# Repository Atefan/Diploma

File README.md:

# Entropy — Hardware True Random Number Generator

ELSYS Sofia diploma project.

## The problem

Computers are deterministic — they can only produce pseudo-random numbers,
which is not good enough for real cryptographic or security-sensitive use
(secure communications, bank transfers, key generation, etc.). This project
builds a **true hardware entropy source** and feeds it directly into the
Linux kernel's entropy pool, so real applications get genuine randomness
instead of PRNG output.

## How it works

1. **Analog front-end** — a custom white-noise generation circuit (charge-pump
   voltage multiplier + PWM stage, op-amp) produces physical noise, sampled
   through the ADC. Schematic and PCB in `Pico_PCB/`.
2. **Firmware** (`Entropy device/`) — runs on a **Raspberry Pi Pico (RP2040,
   dual-core)**. One core samples the ADC and drives the PWM/noise circuit;
   the noise is buffered in a circular queue and streamed to the host over
   USB. Built with the Pico SDK + CMake.
3. **Linux kernel driver** (`driver/`) — a USB driver (`usb_entropy` module)
   that reads the incoming stream and exposes it as `/dev/entropy`, feeding
   it straight into the kernel's entropy pool via `linux/random.h`.
4. **GUI** (`GUI/`) — an SDL2-based Windows app that visualizes the live
   entropy output in real time.
5. **Validation** (`testing/`) — randomness was verified with the NIST Statistical Test Suite (STS 2.1.2, vendored here).

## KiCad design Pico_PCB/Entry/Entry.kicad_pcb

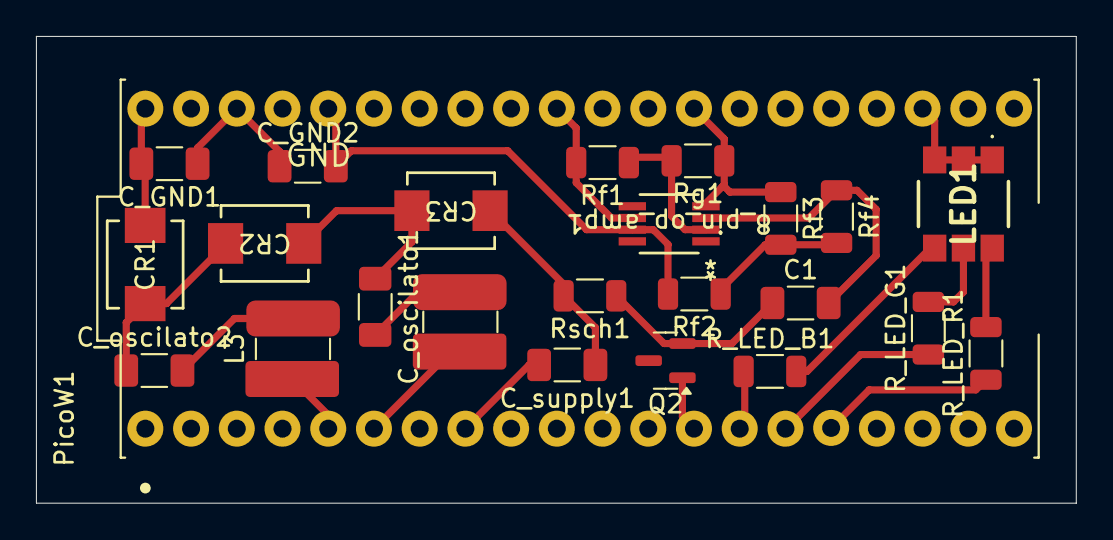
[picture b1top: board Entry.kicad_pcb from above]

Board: 2 copper layers, 57.8 x 25.9 mm, 24 parts (0 on the bottom side), 25 nets.

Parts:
8_pin_op_amp1: MCP6L91RT-EMS; MSOP8_MC_MCH
C1: .1uF; C_1206_3216Metric_Pad1.33x1.80mm_HandSolder
CR1, CR2, CR3: MBRS1100T3G; SMB_403A-03_ONS
C_GND1, C_GND2: .1uF; C_1206_3216Metric_Pad1.33x1.80mm_HandSolder
C_oscilato1, C_oscilato2: .1uF; C_1206_3216Metric_Pad1.33x1.80mm_HandSolder
C_supply1: .1uF; C_1206_3216Metric_Pad1.33x1.80mm_HandSolder
L1, L3: L; L_Coilcraft_LPS4414
LED1: MP008253
PicoW1: SC0918; MODULE_SC0918
Q2: 2n3904; SOT-23
R_LED_B1: 220; R_1206_3216Metric
R_LED_G1: 220; R_1206_3216Metric
R_LED_R1: 220; R_1206_3216Metric
Rf1: 680k; R_1206_3216Metric
Rf2: 120; R_1206_3216Metric
Rf3: 15K; R_1206_3216Metric
Rf4: 1k; R_1206_3216Metric
Rg1: 10k; R_1206_3216Metric
Rsch1: 1M; R_1206_3216Metric

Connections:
5V: CR1.2, C_GND1.2, PicoW1.40 (VBUS)
GND_8: C_supply1.2, PicoW1.8 (GND)
GND_13: PicoW1.13 (GND), Q2.1 (B)
GND_23: LED1.1 (K_RED), LED1.3 (K_GREEN), LED1.5 (K_BLUE), PicoW1.23 (GND)
GND_28: 8_pin_op_amp1.4 (V-), PicoW1.28 (GND), Rf3.1, Rg1.1
GND_38: C_GND1.1, C_GND2.1, PicoW1.38 (GND)
unnamed: 8_pin_op_amp1.2 (-), Rf1.1, Rg1.2
unnamed: 8_pin_op_amp1.7 (V+), C_GND2.2, PicoW1.36 (3V3_OUT), Rf2.2
unnamed: CR1.1, CR2.2, C_oscilato2.1
unnamed: CR2.1, CR3.2, C_oscilato1.1
unnamed: CR3.1, C_supply1.1, Rsch1.2
unnamed: C_oscilato1.2, L1.2
unnamed: C_oscilato2.2, L3.2
unnamed: L3.1, PicoW1.5 (GP3)
unnamed: L1.1, PicoW1.6 (GP4)
unnamed: PicoW1.14 (GP10), R_LED_B1.1
unnamed: PicoW1.15 (GP11), R_LED_G1.1
unnamed: PicoW1.16 (GP12), R_LED_R1.1
unnamed: C1.1, Q2.2 (E), Rsch1.1
unnamed: Rf2.1, Rf3.2, Rf4.2
Signal: 8_pin_op_amp1.3 (+), C1.2, Rf4.1
Vout: 8_pin_op_amp1.6, PicoW1.31 (GP26), Rf1.2
blue: LED1.6 (A_BLUE), R_LED_B1.2
green: LED1.4 (A_GREEN), R_LED_G1.2
red: LED1.2 (A_RED), R_LED_R1.2

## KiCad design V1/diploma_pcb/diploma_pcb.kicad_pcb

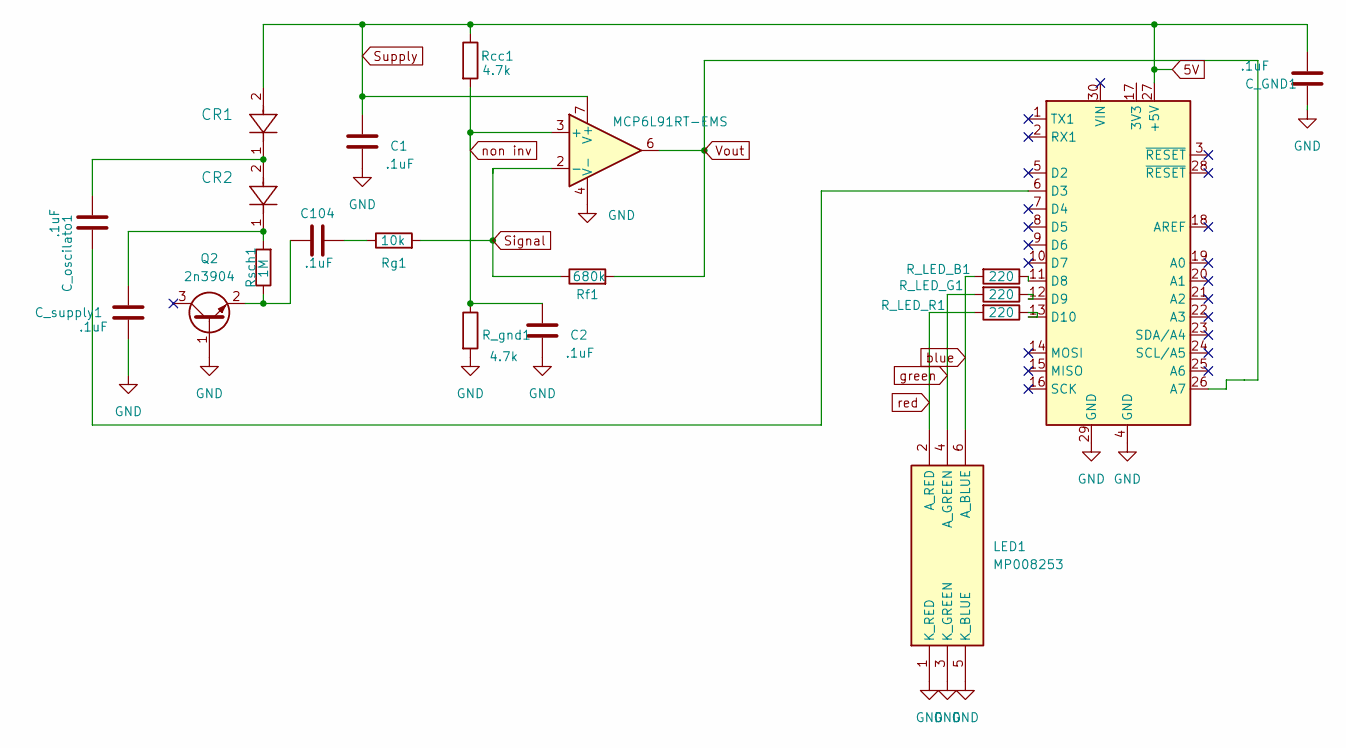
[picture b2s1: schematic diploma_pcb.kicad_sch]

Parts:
8_pin_op_amp1: MCP6L91RT-EMS; MSOP8_MC_MCH
A1: Arduino_Nano_Every; Arduino_Nano
C1, C2, C104: .1uF; C_1206_3216Metric_Pad1.33x1.80mm_HandSolder
CR1, CR2: MBRS1100T3G; SMB_403A-03_ONS
C_GND1: .1uF; C_1206_3216Metric_Pad1.33x1.80mm_HandSolder
C_oscilato1: .1uF; C_1206_3216Metric_Pad1.33x1.80mm_HandSolder
C_supply1: .1uF; C_1206_3216Metric_Pad1.33x1.80mm_HandSolder
LED1: MP008253; Manufacturer_Part_Number MP008253
Q2: 2n3904; SOT-23
R_LED_B1: 220; R_1206_3216Metric
R_LED_G1: 220; R_1206_3216Metric
R_LED_R1: 220; R_1206_3216Metric
R_gnd1: 4.7k; R_1206_3216Metric
Rcc1: 4.7k; R_1206_3216Metric
Rf1: 680k; R_1206_3216Metric
Rg1: 10k; R_1206_3216Metric
Rsch1: 1M; R_1206_3216Metric

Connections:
5V: 8_pin_op_amp1.7 (V+), A1.27 (+5V), C1.1, CR1.2, C_GND1.2, Rcc1.1
GND: 8_pin_op_amp1.4 (V-), A1.4 (GND), A1.29 (GND), C1.2, C2.2, C_GND1.1, C_supply1.2, LED1.1 (K_RED), LED1.3 (K_GREEN), LED1.5 (K_BLUE), Q2.1 (B), R_gnd1.2
unnamed: A1.6 (D3), C_oscilato1.2
unnamed: A1.11 (D8), R_LED_B1.1
unnamed: A1.12 (D9), R_LED_G1.1
unnamed: A1.13 (D10), R_LED_R1.1
unnamed: C104.2, Rg1.1
unnamed: CR1.1, CR2.2, C_oscilato1.1
unnamed: CR2.1, C_supply1.1, Rsch1.2
unnamed: C104.1, Q2.2 (E), Rsch1.1
Signal: 8_pin_op_amp1.2 (-), Rf1.1, Rg1.2
Vout: 8_pin_op_amp1.6, A1.26 (A7), Rf1.2
blue: LED1.6 (A_BLUE), R_LED_B1.2
green: LED1.4 (A_GREEN), R_LED_G1.2
non inv: 8_pin_op_amp1.3 (+), C2.1, R_gnd1.1, Rcc1.2
red: LED1.2 (A_RED), R_LED_R1.2

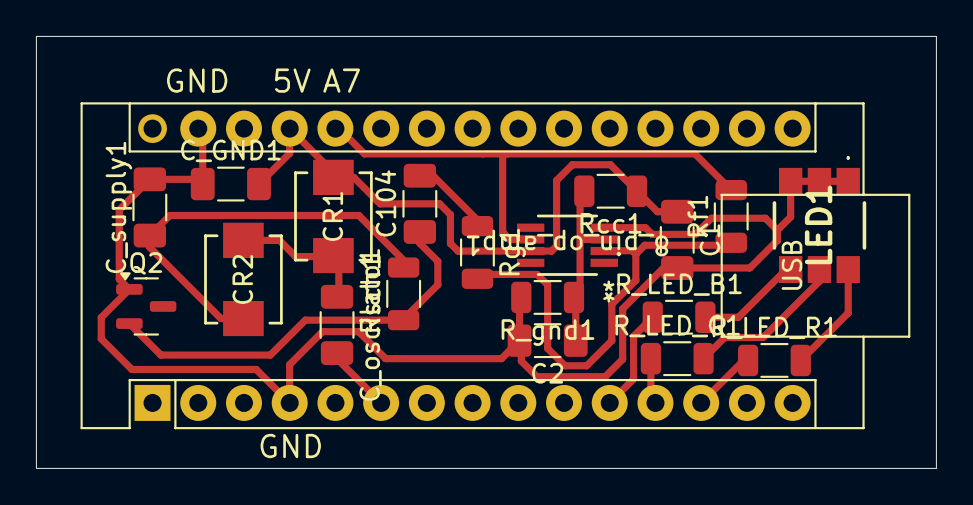
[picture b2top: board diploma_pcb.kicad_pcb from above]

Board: 2 copper layers, 50.0 x 24.0 mm, 20 parts (0 on the bottom side), 16 nets.

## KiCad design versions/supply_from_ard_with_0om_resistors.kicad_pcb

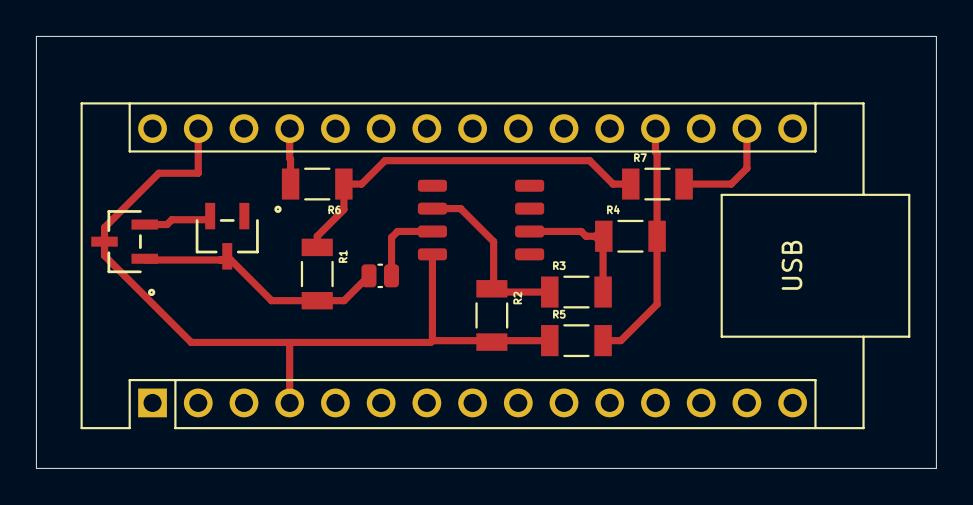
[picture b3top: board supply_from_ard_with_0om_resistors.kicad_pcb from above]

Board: 2 copper layers, 50.0 x 24.0 mm, 12 parts (0 on the bottom side), 10 nets.

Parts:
A1: Arduino_Nano_Every; Arduino_Nano
C104: .1uF; C_0504_1310Metric_Pad0.83x1.28mm_HandSolder
Q1, Q3: 2SC3356; SOT-23_MINIMOLD_REN
R1: 3k3; RESC3116X65N
R2, R3, R4, R5, R6, R7: R; RESC3116X65N
U2: LM741; LM386_custom

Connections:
unnamed: A1.17 (3V3), R7.2
unnamed: A1.27 (+5V), R6.2
unnamed: A1.19 (A0), R4.2, R5.2
unnamed: Q1.2 (B), Q3.2 (B)
unnamed: C104.1, Q1.3 (C), Q3.1 (E), R1.2
unnamed: A1.4 (GND), A1.29 (GND), Q3.3 (C), R2.2, R5.1, U2.4 (V-)
unnamed: R1.1, R6.1, R7.1
unnamed: R3.2, R4.1, U2.6
unnamed: C104.2, U2.3 (+)
unnamed: R2.1, R3.1, U2.2 (-)

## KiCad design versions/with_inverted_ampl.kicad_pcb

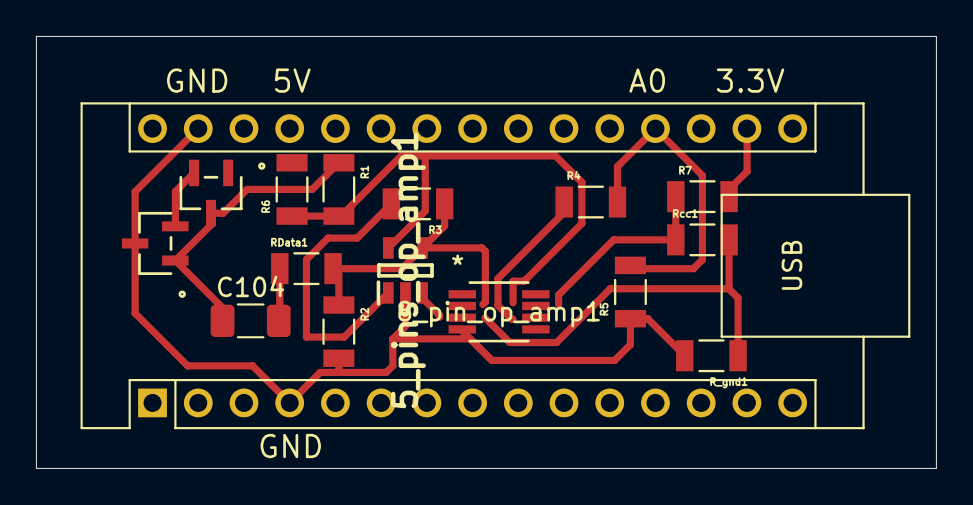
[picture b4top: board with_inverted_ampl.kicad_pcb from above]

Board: 2 copper layers, 50.0 x 24.0 mm, 16 parts (0 on the bottom side), 11 nets.

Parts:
5_pins_op_amp1: MCP6291T-E_OT; SOT95P280X145-5N
8_pin_op_amp1: MCP6L91RT-EMS; MSOP8_MC_MCH
A1: Arduino_Nano_Every; Arduino_Nano
C104: .1uF; C_1206_3216Metric_Pad1.33x1.80mm_HandSolder
Q1, Q3: 2SC3356; SOT-23_MINIMOLD_REN
R1, R2, R3, R4, R5, R6, R7: R; RESC3116X65N
RData1: R; RESC3116X65N
R_gnd1: R; RESC3116X65N
Rcc1: R; RESC3116X65N

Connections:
unnamed: 5_pins_op_amp1.5 (VDD), 8_pin_op_amp1.7 (V+), R1.2, R6.1, R7.1, Rcc1.1
unnamed: 5_pins_op_amp1.3 (VIN+), 8_pin_op_amp1.3 (+), R_gnd1.1, Rcc1.2
unnamed: 5_pins_op_amp1.4 (VIN-), 8_pin_op_amp1.2 (-), R2.1, R3.1, RData1.2
unnamed: 5_pins_op_amp1.1 (VOUT), 8_pin_op_amp1.6, R3.2, R4.1
unnamed: 5_pins_op_amp1.2 (VSS), 8_pin_op_amp1.4 (V-), A1.4 (GND), A1.29 (GND), Q3.3 (C), R2.2, R5.1, R_gnd1.2
unnamed: A1.17 (3V3), R7.2
unnamed: A1.27 (+5V), R6.2
unnamed: A1.19 (A0), R4.2, R5.2
unnamed: C104.2, RData1.1
unnamed: Q1.2 (B), Q3.2 (B)
unnamed: C104.1, Q1.3 (C), Q3.1 (E), R1.1

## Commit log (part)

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2024-10-03 ground commit untill now
2024-10-04 asdasd
2024-10-07 with capacitors
2024-10-09 Fixed schematic with dimplomer
2024-10-09 added Documentation
2024-10-10 with MVS, docs, parts
2024-10-10 rgb placed
2024-10-14 Working Serial Comunication!
2024-10-14 Fixed arduino code(deleted useless files)
2024-10-14 Fixes on PCB
2024-10-15 Ard Code Blinking when receiving and writing constantily things
2024-10-15 MVS code successfully sending and receiving chars(communication successful)
2024-10-15 a few tests written, and passed
2024-10-15 SRAND failed, successfully
2024-10-16 fixed PCB/Word
2024-10-18 tests, giving feedback and added enthropy tests
2024-10-18 documentaion changes
2024-10-22 NIST Tests and Test Code running successfully
2024-10-23 created the driver folder and simple char driver
2024-10-24 usb code start
2024-10-25 docs changes
2024-10-30 kernal module setup and load
2024-10-31 SDL setup and driver modifics
2024-11-04 started the us, doesnt display points
2024-11-05 fixed dots displaying
2024-11-05 changes on schematic
2024-11-06 Led added in Ard
2024-11-07 PCB values chosen and set
2024-11-07 Ard listening, sending spec data
2024-11-07 Button created and text added
2024-11-08 array of obj
2024-11-11 PCB added cap, larger pads, partialy fixed footprints
2024-11-13 Divided in files, not made the showcase of the number
2024-11-14 SDL running 8 bit rngs
2024-11-14 Visualizer 1.0 working, ard in developmen
2024-11-14 stream button added: !Bug with reloading data from serial
2024-11-15 GUI fixed! Some Speed problems
2024-11-18 ARD code added
2024-11-18 changes to ard, file button reader
2024-11-26 arduino comunicating with GUI, PWM woriking
2024-11-28 mods on PCB, Matplot, ?ard?
2024-11-29 PCB fixed Schottkey, Ard code with Union, GNU with bit save
2024-12-03 Faster Serial, tests set, Ard code tweeked
2024-12-05 Schematic, GNU, matplot, Ard code - Done
2024-12-09 Starting driver
2024-12-10 Daemon created, Footprint Assigned, Device constatnly sending
2024-12-12 PCB created (not checked), ard changes?, Footprints set up
2024-12-22 driver communicating and functioning successfully
2025-01-04 kicad Entry done
2025-01-04 Device V1 (queues, usb, multithread)
2025-01-09 versions assigned, /dev/Entropy working
2025-01-13 Struccter fixed, Docs Started, No URBS
2025-01-16 Docs edited 1V
2025-01-20 Documentation solid V1
2025-02-06 Final commit 1
2025-02-06 Final commit 2(no unwanted files)
2025-02-07 final commit 2
